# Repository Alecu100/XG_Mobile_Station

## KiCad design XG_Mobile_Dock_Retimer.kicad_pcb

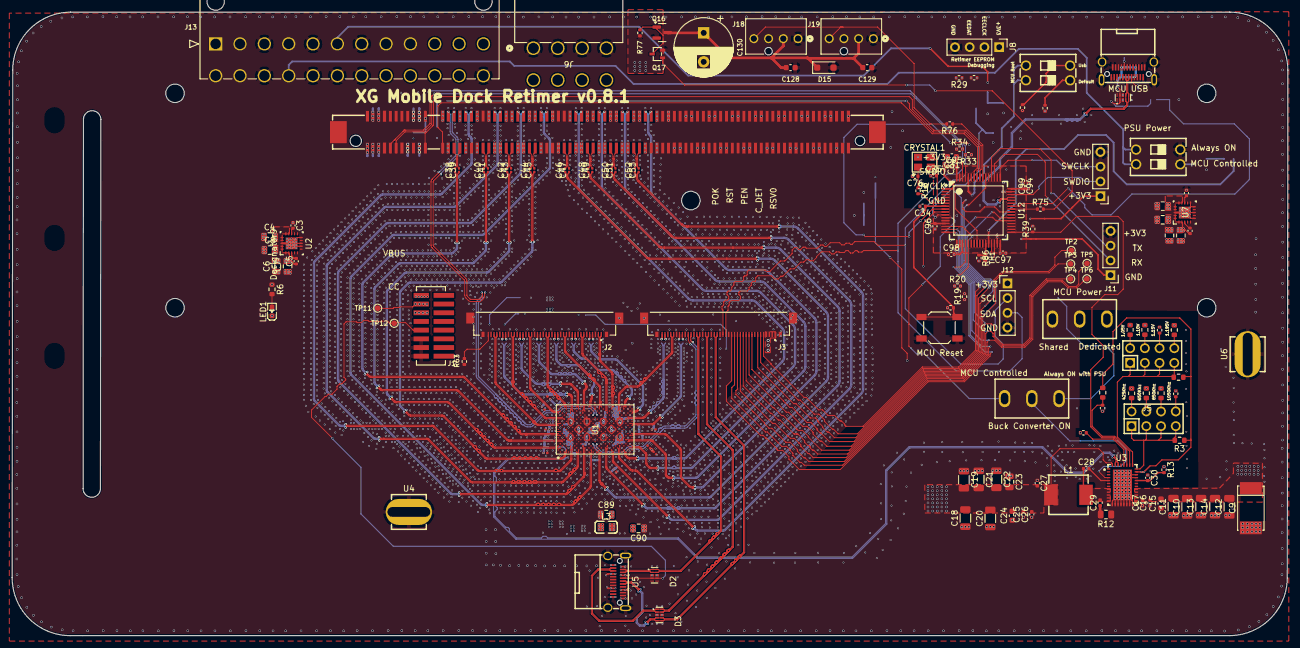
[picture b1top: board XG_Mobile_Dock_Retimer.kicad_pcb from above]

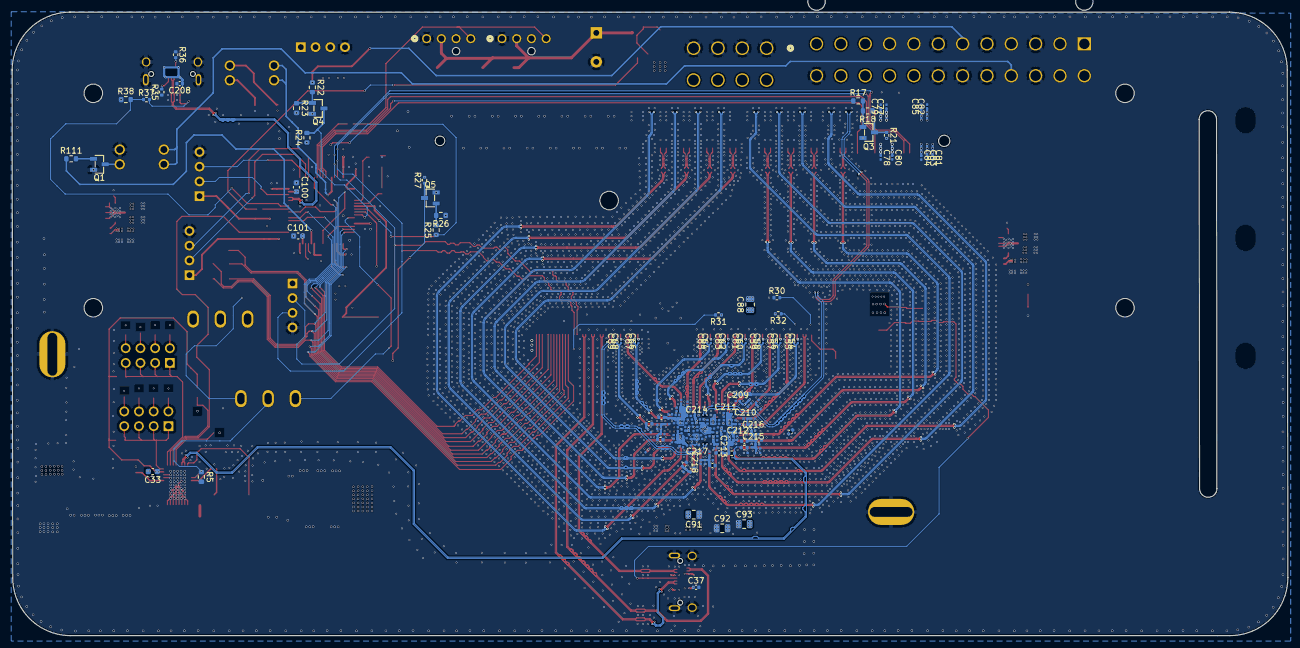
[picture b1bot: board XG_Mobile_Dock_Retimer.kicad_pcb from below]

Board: 8 copper layers, 220.1 x 107.6 mm, 324 parts (170 on the bottom side), 208 nets.

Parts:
C1, C3, C5, C70: 10nF; C_0402_1005Metric
C2, C4, C6, C71: 47uF; C_0805_2012Metric
C7, C8, C23, C72, C73, C88, C89, C90, C91, C92, C93: 10uF; C_0805_2012Metric
C9: 100uF; CAP-SMD_L7.3-W4.3
C10, C11, C12, C13, C14: 22uF; C_1206_3216Metric
C15, C33: 4.7uF; C_0603_1608Metric
C16, C25: 1uF; C_0402_1005Metric
C17, C27, C28: 0.1uF; C_0402_1005Metric
C18, C19: 220uF; C_1206_3216Metric
C20, C21: 100uF; C_1206_3216Metric
C22: 47uF; C_1206_3216Metric
C24: 3.3uF; C_0603_1608Metric
C26: 0.47uF; C_0402_1005Metric
C29: 1nFt; C_0402_1005Metric
C30: 4.7uF; C_0402_1005Metric
C31: 1µF; C_0603_1608Metric
C32, C34, C94, C95, C96, C97, C98: 0.1µF; C_0402_1005Metric
C35, C36, C74, C86, C87, C102, C103, C104, C105, C111, C112, C113, C114, C115, C116, C117, C118, C162, C163, C164, C187, C188, C201, C204, C205, C206, C209, C210, C211, C212, C213, C214, C215, C216, C217: 100nF; C_0201_0603Metric
C37, C208: 0.1μF; C_0402_1005Metric
C38, C39, C40, C41, C42, C43, C44, C45, C46, C47, C48, C49, C50, C51, C52, C53, C54, C55, C56, C57, C58, C59, C60, C61, C62, C63, C64, C65, C66, C67, C68, C69, C77, C78, C79, C80, C81, C82, C83, C84, C85: 220nF; C_0201_0603Metric
C75, C76: 15pF; C_0402_1005Metric
C99: 4.7µF; C_0402_1005Metric
C100, C101: 2.2µF; C_0603_1608Metric
C106, C107, C108, C109, C110, C192, C193, C218: 1uF; C_0201_0603Metric
C119, C120, C121, C122, C123, C124, C125, C126, C203, C207: 10uF; C_0402_1005Metric
C127, C131, C132, C133, C134, C135, C136, C137, C138, C139, C140, C141, C142, C143, C144, C145, C146, C147, C148, C149, C150, C151, C179, C180, C186: 100nF; C_0201_0603Metric_Tight
C128, C129: 0.1µF; C_0603_1608Metric
C130: 470µF; CP_Radial_D10.0mm_P5.00mm
C152, C153, C154, C155, C157, C160, C161: 100nF; C_0201_0603Metric_Tight23
C156, C158, C159, C165, C166, C167, C168, C169, C170, C171, C172, C173, C174, C175, C176, C177, C178, C181, C182, C183, C184, C185: 10nF; C_0201_0603Metric_Tight
C189, C190, C194, C195, C196, C197, C198, C199, C200: 1uF; C_0201_0603Metric_Tight
C191, C202: 1uF; C_0201_0603Metric_Tight23
CRYSTAL1: 8MHz; CRYSTAL-SMD_4P-L3.2-W2.5-BL_SIT8008BI
D1, D2, D3: H5VU25U; AZ1045-04F
D15: 1N4007; D_SOD-123F
H1, H2: HDR-TH_8P-P2.54-V-M-R2-C4-S2.54
J1: 5-1775443-8
J2, J3: 20455-040E-76
J4, J5: FL_001
J6: 353180820; CONN_SD-35318-xxxx_08_MOL
J7: CEE016400140111; CONN-SMD_164P-P1.00-CEE016400140111
J8: Retimer EEPROM; PinHeader_1x04_P2.54mm_Vertical
J10: SWD; PinHeader_1x04_P2.54mm_Vertical
J11: UART; PinHeader_1x04_P2.54mm_Vertical
J12: I2C1; PinHeader_1x04_P2.54mm_Vertical
J13: 39301240; CON_39300240
J18, J19: CONN_SD-47053-001_H10p00_MOL
L1: 1uH; IND-SMD_L7.7-W6.6_APS0630
L3: FBMJ2125HS420-T; L0805
LED1: LED0603-RD
Q1, Q3, Q4, Q5: SOT-23-3_L2.9-W1.3-P1.90-LS2.4-BR
Q16: AO3401A; SOT-23
Q17: 2N7002W; SOT-323-3_L2.0-W1.3-P1.30-LS2.1-BR
R1, R3, R9, R18, R22, R26, R38: 100k; R_0603_1608Metric
R2, R41: 133k; R_0402_1005Metric
R4, R5: 22.1k; R_0603_1608Metric
R6: 200; R_0603_1608Metric
R7: 174; R_0402_1005Metric
R8, R33, R34, R63, R77, R85: 10k; R_0402_1005Metric
R10, R37, R39: 42.2k; R_0402_1005Metric
R11: 30.1k; R_0402_1005Metric
R12: 1; R_0805_2012Metric
R13: 1; R_0402_1005Metric
R14, R15: 33; R_0201_0603Metric
R16: 150; R_0402_1005Metric
R17, R25, R111: 4k; R_0603_1608Metric
R19, R20, R21, R27, R28, R29: 4.7k; R_0402_1005Metric
R23: 470k; R_0603_1608Metric
R24: 10k; R_0603_1608Metric
R30, R31, R32, R46, R84: 1k; R_0402_1005Metric
R35, R36: 5.1k; R_0402_1005Metric
R40: 60.4k; R_0603_1608Metric
R42: 4.64k; R_0603_1608Metric
R43: 110k; R_0603_1608Metric
R44: 90.9k; R_0603_1608Metric
R45: 165k; R_0603_1608Metric
R75: 100; R_0402_1005Metric
R76: 330; R_0402_1005Metric
R86: 100k; R_0402_1005Metric
SW1: SW_Push; SW_SPST_SKQG_WithStem
SW2, SW4: SW-TH_SS-12D10L5
SW3, SW30: SW-TH_DSWB02LHGET
TH1: NCP15WF104F03RC; R_0402_1005Metric
TP2, TP3, TP4, TP5, TP6, TP11, TP12: TestPoint_Small; TestPoint_Pad_D1.0mm
U1: DS160PT801ACBR; ACB0332A-IPC_A
U2, U7: TPS7A8400ARGRR; RGR0020A
U3: LQFN-CLIP-40_L7.0-W5.0-P0.50-TL-EP
U4, U6: CONN-SMD_T31000
U5, U8: USB-C-SMD_GT-USB-7091A
U12: LQFP-64_L10.0-W10.0-P0.50-LS12.0-BL

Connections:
+1V8: C5.1, C6.2, C7.2, C8.2, C87.2, C88.1, C157.2, C160.1, C161.1, C192.1, C193.1, R6.1, R31.1, R32.2, U1.AE12 (PWR_1), U1.AF11 (PWR_1), U1.AF13 (PWR_1), U1.AG10 (PWR_1), U1.AG14 (PWR_1), U1.AH11 (PWR_1), U1.AH13 (PWR_1), U1.AJ12 (PWR_1), U1.J12 (PWR_1), U1.K11 (PWR_1), U1.K13 (PWR_1), U1.L10 (PWR_1), U1.L14 (PWR_1), U1.M11 (PWR_1), U1.M13 (PWR_1), U1.N12 (PWR_1), U2.1 (OUT), U2.2 (SNS), U2.19 (OUT), U2.20 (OUT)
+1V17_1: C93.2, C152.1, C153.1, C154.1, C155.1, C191.1, C202.1, C213.1, C214.1, L3.1, U1.AB15 (PWR_2_A), U1.AB17 (PWR_2_A), U1.AC14 (PWR_2_A), U1.AD15 (PWR_2_A), U1.AD17 (PWR_2_A), U1.P7 (PWR_2_A), U1.P9 (PWR_2_A), U1.R10 (PWR_2_A), U1.T7 (PWR_2_A), U1.T9 (PWR_2_A)
+1V17_2: C18.2, C19.2, C20.2, C21.2, C22.2, C23.2, C24.2, C25.2, C26.2, C27.2, C35.1, C36.1, C74.1, C86.1, C89.2, C90.2, C91.2, C92.2, C102.1, C103.1, C104.1, C105.1, C106.1, C107.1, C108.1, C109.1, C110.1, C111.1, C112.1, C113.1, C114.1, C115.1, C116.2, C117.2, C118.2, C119.2, C120.2, C121.2, C122.2, C123.2, C124.2, C125.2, C126.2, C127.1, C131.1, C132.1, C133.1, C134.1, C135.1, C136.1, C137.1, C138.1, C139.1, C140.1, C141.1, C142.1, C143.1, C144.1, C145.1, C146.1, C147.1, C148.1, C149.1, C150.1, C151.1, C156.2, C158.2, C159.2, C162.2, C163.2, C164.2, C165.2, C166.2, C167.2, C168.2, C169.2, C170.2, C171.2, C172.2, C173.2, C174.2, C175.2, C176.2, C177.2, C178.2, C179.1, C180.1, C181.2, C182.2, C183.2, C184.2, C185.2, C186.1, C187.2, C188.2, C189.2, C190.2, C194.2, C195.1, C196.1, C197.1, C198.1, C199.2, C200.1, C201.2, C203.2, C204.2, C205.2, C206.2, C207.2, C209.2, C210.2, C211.2, C212.2, C215.2, C216.2, C217.2, C218.2, L1.1, L3.2, R7.1, U1.AA12 (PWR2_HS_D), U1.AB7 (PWR2_HS_A), U1.AB9 (PWR2_HS_A), U1.AC10 (PWR2_HS_D), U1.AD7 (PWR2_HS_A), U1.AD9 (PWR2_HS_A), U1.AK7 (PWR2_HS_A), U1.AK9 (PWR2_HS_D), U1.AK15 (PWR2_HS_D), U1.AK17 (PWR2_HS_A), U1.AL10 (PWR2_HS_D), U1.AL14 (PWR2_HS_D), U1.AM7 (PWR2_HS_A), U1.AM9 (PWR2_HS_D), U1.AM15 (PWR2_HS_D), U1.AM17 (PWR2_HS_A), U1.F7 (PWR2_HS_A), U1.F9 (PWR2_HS_D), U1.F15 (PWR2_HS_D), U1.F17 (PWR2_HS_A), U1.G10 (PWR2_HS_D), U1.G14 (PWR2_HS_D), U1.H7 (PWR2_HS_A), U1.H9 (PWR2_HS_D), U1.H15 (PWR2_HS_D), U1.H17 (PWR2_HS_A), U1.P15 (PWR2_HS_A), U1.P17 (PWR2_HS_A), U1.R14 (PWR2_HS_D), U1.T15 (PWR2_HS_A), U1.T17 (PWR2_HS_A), U1.U12 (PWR2_HS_D), U1.V11 (PWR2_HS_D), U1.V13 (PWR2_HS_A), U1.W10 (PWR2_HS_A), U1.W14 (PWR2_HS_A), U1.Y11 (PWR2_HS_A), U1.Y13 (PWR2_HS_D), U3.40 (VOSNS)
+3V3: C4.2, C77.1, C78.1, C79.1, C80.1, J7.A9, J7.A10, J7.B8, J7.B10, J8.1, J13.1, J13.2, J13.12, J13.13, R21.2, R27.2, R28.2, R29.2, SW2.3, SW4.3, U2.14 (EN), U2.15 (IN), U2.16 (IN), U2.17 (IN)
+3V3MCU: C31.1, C32.2, C94.2, C95.2, C96.2, C97.2, C98.2, C99.1, J3.1 (+3.3V), J3.2 (+3.3V), J3.3 (+3.3V), J3.4 (+3.3V), J10.1, J11.1, J12.1, R19.1, R20.1, R24.1, R33.1, R34.1, R39.2, R46.1, R85.2, R86.2, SW4.2, U12.1 (VBAT), U12.13 (VDDA), U12.19 (VDD), U12.32 (VDD), U12.48 (VDD), U12.64 (VDD)
+3V3SB: C70.1, C71.2, C72.2, C73.2, SW4.1, U7.1 (OUT), U7.2 (SNS), U7.19 (OUT), U7.20 (OUT)
+5VSB: C2.2, J13.9, U7.14 (EN), U7.15 (IN), U7.16 (IN), U7.17 (IN)
+12V: C9.1, C10.2, C11.2, C12.2, C13.2, C14.2, C15.2, C16.2, C17.2, C81.1, C82.1, C83.1, C84.1, C85.1, J6.5, J6.6, J6.7, J6.8, J7.A2, J7.A3, J7.B1, J7.B2, J7.B3, J13.10, J13.11, Q16.2 (S), R13.1, R77.1, U3.21 (PVIN), U3.22 (PVIN), U3.23 (PVIN), U3.24 (PVIN), U3.25 (PVIN)
/AC_LOSS: J3.15 (P_AC_LOSS), U12.20 (PA4)
/BP: C33.1, R1.1, R3.1, R9.1, U3.31 (BP)
/BUCK_ON: R5.1, SW2.2, U3.4 (EN_UVLO)
/BUCK_ON_MCU: SW2.1, U12.11 (PC3)
/CC: D2.4 (I/O_3), D2.7 (NC), J1.13 (CC), TP12.1 (1_1), U5.A5 (CC1)
/CLKN: J3.30 (PCIE_CLKN), U1.V5 (REFCLK-)
/CLKOUTN: J7.A14, R15.2
/CLKOUTP: J7.A13, R14.2
/CLKOUT_T_N: R15.1, U1.V19 (REFCLKOUT-)
/CLKOUT_T_P: R14.1, U1.Y19 (REFCLKOUT+)
/CLKP: J3.31 (PCIE_CLKP), U1.Y5 (REFCLK+)
/CLKREQ#: J7.B12, U12.58 (PB6)
/CLKREQ_RETIMER#: U1.B11 (CLKREQ_N), U12.9 (PC1)
/CON_DET: J3.11 (CON_DET), TP3.1 (1_1), U12.14 (PA0-WKUP(PA0))
/C_DN: D3.5 (I/O_4), D3.6 (NC), J3.21 (USB_DM), U5.A7 (D-)
/C_DP: D3.4 (I/O_3), D3.7 (NC), J3.22 (USB_DP), U5.A6 (D+)
/C_RXN: D3.2 (I/O_2), D3.9 (NC), J3.24 (USB_RXN), U5.B11 (Rx1+)
/C_RXP: D3.1 (I/O_1), D3.10 (NC), J3.25 (USB_RXP), U5.B10 (RX1-)
/C_TXN: D2.1 (I/O_1), D2.10 (NC), J3.28 (USB_TXP), U5.A2 (TX1+)
/C_TXP: D2.2 (I/O_2), D2.9 (NC), J3.27 (USB_TXN), U5.A3 (TX1-)
/DET: J2.40 (CON_DET_TOWER#), R63.1
/EE_CLCK: J8.2, R28.1, U1.AP11 (EE_CLK)
/EE_DAT: J8.3, R29.1, U1.AP13 (EE_DAT)
/FSEL: H2.1, H2.3, H2.5, H2.7, R3.2, U3.32 (FSEL)
/HSI0N: C55.2, J2.34 (PCIE_RXN0)
/HSI0P: C54.2, J2.35 (PCIE_RXP0)
/HSI1N: C57.2, J2.28 (PCIE_RXN1)
/HSI1P: C56.2, J2.29 (PCIE_RXP1)
/HSI2N: C59.2, J2.22 (PCIE_RXN2)
/HSI2P: C58.2, J2.23 (PCIE_RXP2)
/HSI3N: C61.2, J2.16 (PCIE_RXN3)
/HSI3P: C60.2, J2.17 (PCIE_RXP3)
/HSI4N: C63.2, J2.10 (PCIE_RXN4)
/HSI4P: C62.2, J2.11 (PCIE_RXP4)
/HSI5N: C65.2, J2.4 (PCIE_RXN5)
/HSI5P: C64.2, J2.5 (PCIE_RXP5)
/HSI6N: C67.2, J3.39 (PCIE_RXN6)
/HSI6P: C66.2, J3.40 (PCIE_RXP6)
/HSI7N: C69.2, J3.33 (PCIE_RXN7)
/HSI7P: C68.2, J3.34 (PCIE_RXP7)
/HSIL0N: J7.A17, U1.G4 (B_PERn0)
/HSIL0P: J7.A16, U1.H3 (B_PERp0)
/HSIL1N: J7.A22, U1.K1 (B_PERn1)
/HSIL1P: J7.A21, U1.L2 (B_PERp1)
/HSIL2N: J7.A26, U1.N4 (B_PERn2)
/HSIL2P: J7.A25, U1.P3 (B_PERp2)
/HSIL3N: J7.A30, U1.T1 (B_PERn3)
/HSIL3P: J7.A29, U1.U2 (B_PERp3)
/HSIL4N: J7.A36, U1.AN2 (B_PERn4)
/HSIL4P: J7.A35, U1.AP1 (B_PERp4)
/HSIL5N: J7.A40, U1.AT3 (B_PERn5)
/HSIL5P: J7.A39, U1.AU4 (B_PERp5)
/HSIL6N: J7.A44, U1.AR6 (B_PERn6)
/HSIL6P: J7.A43, U1.AP7 (B_PERp6)
/HSIL7N: J7.A48, U1.AT9 (B_PERn7)
/HSIL7P: J7.A47, U1.AU10 (B_PERp7)
/HSIT0N: C55.1, U1.H21 (B_PETp0)
/HSIT0P: C54.1, U1.G20 (B_PETn0)
/HSIT1N: C57.1, U1.L22 (B_PETp1)
/HSIT1P: C56.1, U1.K23 (B_PETn1)
/HSIT2N: C59.1, U1.P21 (B_PETp2)
/HSIT2P: C58.1, U1.N20 (B_PETn2)
/HSIT3N: C61.1, U1.U22 (B_PETp3)
/HSIT3P: C60.1, U1.T23 (B_PETn3)
/HSIT4N: C63.1, U1.AP23 (B_PETp4)
/HSIT4P: C62.1, U1.AN22 (B_PETn4)
/HSIT5N: C65.1, U1.AU20 (B_PETp5)
/HSIT5P: C64.1, U1.AT21 (B_PETn5)
/HSIT6N: C67.1, U1.AP17 (B_PETp6)
/HSIT6P: C66.1, U1.AR18 (B_PETn6)
/HSIT7N: C69.1, U1.AU14 (B_PETp7)
/HSIT7P: C68.1, U1.AT15 (B_PETn7)
/HSO0N: C39.2, J7.B15
/HSO0P: C38.2, J7.B14
/HSO1N: C41.2, J7.B20
/HSO1P: C40.2, J7.B19
/HSO2N: C43.2, J7.B24
/HSO2P: C42.2, J7.B23
/HSO3N: C45.2, J7.B28
/HSO3P: C44.2, J7.B27
/HSO4N: C47.2, J7.B34
/HSO4P: C46.2, J7.B33
/HSO5N: C49.2, J7.B38
/HSO5P: C48.2, J7.B37
/HSO6N: C51.2, J7.B42
/HSO6P: C50.2, J7.B41
/HSO7N: C53.2, J7.B46
/HSO7P: C52.2, J7.B45
/HSOL0N: J2.37 (PCIE_TXN0), U1.B15 (A_PERp0)
/HSOL0P: J2.38 (PCIE_TXP0), U1.A14 (A_PERn0)
/HSOL1N: J2.31 (PCIE_TXN1), U1.C18 (A_PERp1)
/HSOL1P: J2.32 (PCIE_TXP1), U1.D17 (A_PERn1)
/HSOL2N: J2.25 (PCIE_TXN2), U1.B21 (A_PERp2)
/HSOL2P: J2.26 (PCIE_TXP2), U1.A20 (A_PERn2)
/HSOL3N: J2.19 (PCIE_TXN3), U1.E22 (A_PERp3)
/HSOL3P: J2.20 (PCIE_TXP3), U1.D23 (A_PERn3)
/HSOL4N: J2.13 (PCIE_TXN4), U1.AB23 (A_PERp4)
/HSOL4P: J2.14 (PCIE_TXP4), U1.AA22 (A_PERn4)
/HSOL5N: J2.7 (PCIE_TXN5), U1.AE20 (A_PERp5)
/HSOL5P: J2.8 (PCIE_TXP5), U1.AD21 (A_PERn5)
/HSOL6N: J2.1 (PCIE_TXN6), U1.AH23 (A_PERp6)
/HSOL6P: J2.2 (PCIE_TXP6), U1.AG22 (A_PERn6)
/HSOL7N: J3.36 (PCIE_TXN7), U1.AL20 (A_PERp7)
/HSOL7P: J3.37 (PCIE_TXP7), U1.AK21 (A_PERn7)
/HSOT0N: C39.1, U1.A10 (A_PETn0)
/HSOT0P: C38.1, U1.B9 (A_PETp0)
/HSOT1N: C41.1, U1.D7 (A_PETn1)
/HSOT1P: C40.1, U1.C6 (A_PETp1)
/HSOT2N: C43.1, U1.A4 (A_PETn2)
/HSOT2P: C42.1, U1.B3 (A_PETp2)
/HSOT3N: C45.1, U1.D1 (A_PETn3)
/HSOT3P: C44.1, U1.E2 (A_PETp3)
/HSOT4N: C47.1, U1.AA2 (A_PETn4)
/HSOT4P: C46.1, U1.AB1 (A_PETp4)
/HSOT5N: C49.1, U1.AD3 (A_PETn5)
/HSOT5P: C48.1, U1.AE4 (A_PETp5)
/HSOT6N: C51.1, U1.AG2 (A_PETn6)
/HSOT6P: C50.1, U1.AH1 (A_PETp6)
/HSOT7N: C53.1, U1.AK3 (A_PETn7)
/HSOT7P: C52.1, U1.AL4 (A_PETp7)
/LED_RED#: J3.7 (LED_R), U12.54 (PD2)
/LED_WHITE#: J3.6 (LED_W), U12.40 (PC9)
/LOCK_DET: J3.9 (CON_SW1_DET), U12.37 (PC6)
/LOCK_SW: J3.5 (LOCK_SW), U12.24 (PC4)
/MCU_IRQ#: J3.16 (MCU_IRQ#), U12.21 (PA5)
/MCU_Retimer/BOOT0: SW3.1, SW3.2, U12.60 (BOOT0)
/MCU_Retimer/FAN_ON: R75.1, U12.41 (PA8)
/MCU_Retimer/FAN_PWM: R76.1, U12.55 (PB3(JTDOTRACESWO))
/MCU_Retimer/RX: J11.3, U12.52 (PC11)
/MCU_Retimer/SWCLK: J10.3, U12.49 (PA14(JTCK-SWCLK))
/MCU_Retimer/SWDIO: J10.2, U12.46 (PA13(JTMS-SWDIO))
/MCU_Retimer/TX: J11.2, U12.51 (PC10)
/MODE: R9.2, R10.1, U3.34 (MODE)
/PERST#: J7.A11, Q3.3 (C), R21.1
/PERST_MCU#: R17.1, U12.57 (PB5)
/PERST_RETIMER#: Q5.3 (C), R27.1, U1.Y1 (PERST_N)
/PERST_RETIMER_MCU#: R25.1, U12.8 (PC0)
/PGOOD_BUCK: R39.1, U3.35 (PGOOD), U12.33 (PB12)
/PRE_IN: C28.1, C29.2, L1.2, U3.8 (SW), U3.9 (SW), U3.10 (SW), U3.11 (SW), U3.12 (SW)
/PSON: R111.1, U12.28 (PB2-BOOT1(PB2))
/PSPWROK: J13.6, R22.1
/PSPWROK3V3: Q4.3 (C), R24.2, U12.10 (PC2)
/PWREN#: J3.12 (PWR_EN#), TP4.1 (1_1), U12.15 (PA1)
/PWROK: J3.14 (PWROK), TP6.1 (1_1), U12.17 (PA3)
/RSP: R7.2, R8.1, U3.39 (RSP)
/RST#: J3.13 (RST#), TP5.1 (1_1), U12.16 (PA2)
/RST_SW: C34.1, R85.1, SW1.1, U12.7 (NRST)
/RSV0: J3.10, TP2.1 (1_1), U12.38 (PC7)
/SCL: J3.19 (SMB1_CLK), J7.B5, J12.2, R33.2, U12.61 (PB8)
/SCL2: R19.2, U1.AC6 (SMBCLK), U12.29 (PB10)
/SDA: J3.18 (SMB1_DAT), J7.B6, J12.3, R34.2, U12.62 (PB9)
/SDA2: R20.2, U1.AG6 (SMBDAT), U12.30 (PB11)
/USBDN: D1.4 (I/O_3), D1.7 (NC), U8.A7 (D-), U12.44 (PA11)
/USBDP: D1.5 (I/O_4), D1.6 (NC), U8.A6 (D+), U12.45 (PA12)
/USBVBUS: R37.1, R38.2, U12.42 (PA9)
/VBUS: C37.1, J1.9 (VBUS), J1.10 (VBUS), J1.11 (VBUS), TP11.1 (1_1), U5.A4 (VBUS), U5.A9 (VBUS), U5.B4 (VBUS), U5.B9 (VBUS)
/VBUS_USB2: C208.1, D1.2 (I/O_2), D1.9 (NC), R37.2, U8.A4 (VBUS), U8.A9 (VBUS), U8.B4 (VBUS), U8.B9 (VBUS)
/VSEL: H1.1, H1.3, H1.5, H1.7, R1.2, U3.33 (VSEL)
/WAKE#: J7.B11, U12.56 (PB4(NJTRST))
GND: C1.1, C2.1, C3.1, C4.1, C6.1, C7.1, C8.1, C9.2, C10.1, C11.1, C12.1, C13.1, C14.1, C15.1, C16.1, C17.1, C18.1, C19.1, C20.1, C21.1, C22.1, C23.1, C24.1, C25.1, C26.1, C27.1, C30.1, C31.2, C32.1, C33.2, C34.2, C35.2, C36.2, C37.2, C71.1, C72.1, C73.1, C74.2, C75.1, C76.2, C77.2, C78.2, C79.2, C80.2, C81.2, C82.2, C83.2, C84.2, C85.2, C86.2, C87.1, C88.2, C89.1, C90.1, C91.1, C92.1, C93.1, C94.1, C95.1, C96.1, C97.1, C98.1, C99.2, C100.1, C101.1, C102.2, C103.2, C104.2, C105.2, C106.2, C107.2, C108.2, C109.2, C110.2, C111.2, C112.2, C113.2, C114.2, C115.2, C116.1, C117.1, C118.1, C119.1, C120.1, C121.1, C122.1, C123.1, C124.1, C125.1, C126.1, C127.2, C128.2, C129.2, C130.2, C131.2, C132.2, C133.2, C134.2, C135.2, C136.2, C137.2, C138.2, C139.2, C140.2, C141.2, C142.2, C143.2, C144.2, C145.2, C146.2, C147.2, C148.2, C149.2, C150.2, C151.2, C152.2, C153.2, C154.2, C155.2, C156.1, C157.1, C158.1, C159.1, C160.2, C161.2, C162.1, C163.1, C164.1, C165.1, C166.1, C167.1, C168.1, C169.1, C170.1, C171.1, C172.1, C173.1, C174.1, C175.1, C176.1, C177.1, C178.1, C179.2, C180.2, C181.1, C182.1, C183.1, C184.1, C185.1, C186.2, C187.1, C188.1, C189.1, C190.1, C191.2, C192.2, C193.2, C194.1, C195.2, C196.2, C197.2, C198.2, C199.1, C200.2, C201.1, C202.2, C203.1, C204.1, C205.1, C206.1, C207.1, C208.2, C209.1, C210.1, C211.1, C212.1, C213.2, C214.2, C215.1, C216.1, C217.1, C218.1, CRYSTAL1.2 (GND), CRYSTAL1.4 (GND), D1.3 (GND), D1.8 (GND), D2.3 (GND), D2.8 (GND), D3.3 (GND), D3.8 (GND), D15.2 (A), J1.14 (GND), J1.15 (GND), J1.16 (GND), J2.3 (GND), J2.6 (GND), J2.9 (GND), J2.12 (GND), J2.15 (GND), J2.18 (GND), J2.21 (GND), J2.24 (GND), J2.27 (GND), J2.30 (GND), J2.33 (GND), J2.36 (GND), J2.39 (GND), J2.S1 (SHIELD), J2.S2 (SHIELD), J2.S3 (SHIELD), J2.S4 (SHIELD), J3.17 (GND), J3.20 (GND), J3.23 (GND), J3.26 (GND), J3.29 (GND), J3.32 (GND), J3.35 (GND), J3.38 (GND), J3.S1 (SHIELD), J3.S2 (SHIELD), J3.S3 (SHIELD), J3.S4 (SHIELD), J6.1, J6.2, J6.3, J6.4, J7.2, J7.A4, J7.A12, J7.A15, J7.A18, J7.A20, J7.A23, J7.A24, J7.A27, J7.A28, J7.A31, J7.A34, J7.A37, J7.A38, J7.A41, J7.A42, J7.A45, J7.A46, J7.A49, J7.A51, J7.A54, J7.A55, J7.A58, J7.A59, J7.A62, J7.A63, J7.A66, J7.A67, J7.A70, J7.A71, J7.A74, J7.A75, J7.A78, J7.A79, J7.A82, J7.B4, J7.B7, J7.B13, J7.B16, J7.B18, J7.B21, J7.B22, J7.B25, J7.B26, J7.B29, J7.B32, J7.B35, J7.B36, J7.B39, J7.B40, J7.B43, J7.B44, J7.B47, J7.B49, J7.B52, J7.B53, J7.B56, J7.B57, J7.B60, J7.B61, J7.B64, J7.B65, J7.B68, J7.B69, J7.B72, J7.B73, J7.B76, J7.B77, J7.B80, J8.4, J10.4, J11.4, J12.4, J13.3, J13.5, J13.7, J13.15, J13.17, J13.18, J13.19, J13.24, J18.1, J19.1, LED1.1 (K), Q1.2 (E), Q3.2 (E), Q4.2 (E), Q5.2 (E), Q17.2 (S), R2.2, R4.2, R5.2, R8.2, R10.2, R11.1, R12.1, R18.1, R23.2, R26.1, R30.1, R35.1, R36.1, R38.1, R40.2, R41.2, R42.2, R43.2, R44.2, R45.2, R63.2, R84.1, SW1.2, SW30.4, TH1.2, U1.A2 (GND), U1.A8 (GND), U1.A16 (GND), U1.A22 (GND), U1.AA4 (GND), U1.AA8 (GND), U1.AA16 (GND), U1.AA20 (GND), U1.AB3 (GND), U1.AB5 (GND), U1.AB11 (GND), U1.AB13 (GND), U1.AB19 (GND), U1.AB21 (GND), U1.AC2 (GND), U1.AC22 (GND), U1.AD5 (GND), U1.AD11 (GND), U1.AD13 (GND), U1.AD19 (GND), U1.AE8 (GND), U1.AE16 (GND), U1.AF1 (GND), U1.AF3 (GND), U1.AF5 (GND), U1.AF7 (GND), U1.AF9 (GND), U1.AF15 (GND), U1.AF17 (GND), U1.AF19 (GND), U1.AF21 (GND), U1.AF23 (GND), U1.AH3 (GND), U1.AH5 (GND), U1.AH7 (GND), U1.AH9 (GND), U1.AH15 (GND), U1.AH17 (GND), U1.AH19 (GND), U1.AH21 (GND), U1.AJ2 (GND), U1.AJ4 (GND), U1.AJ8 (GND), U1.AJ16 (GND), U1.AJ20 (GND), U1.AJ22 (GND), U1.AK5 (GND), U1.AK11 (GND), U1.AK13 (GND), U1.AK19 (GND), U1.AL6 (GND), U1.AL18 (GND), U1.AM1 (GND), U1.AM3 (GND), U1.AM5 (GND), U1.AM11 (GND), U1.AM13 (GND), U1.AM19 (GND), U1.AM21 (GND), U1.AM23 (GND), U1.AN4 (GND), U1.AN8 (GND), U1.AN12 (GND), U1.AN16 (GND), U1.AN20 (GND), U1.AP5 (GND), U1.AP9 (GND), U1.AP15 (GND), U1.AP19 (GND), U1.AR2 (GND), U1.AR4 (GND), U1.AR8 (GND), U1.AR10 (GND), U1.AR14 (GND), U1.AR16 (GND), U1.AR20 (GND), U1.AR22 (GND), U1.AT1 (GND_NC), U1.AT5 (GND), U1.AT11 (GND), U1.AT19 (GND), U1.AT23 (GND_NC), U1.AU2 (GND), U1.AU8 (GND), U1.AU16 (GND), U1.AU22 (GND), U1.B1 (GND_NC), U1.B5 (GND), U1.B13 (GND), U1.B19 (GND), U1.B23 (GND_NC), U1.C2 (GND), U1.C4 (GND), U1.C8 (GND), U1.C10 (GND), U1.C14 (GND), U1.C16 (GND), U1.C20 (GND), U1.C22 (GND), U1.D5 (GND), U1.D9 (GND), U1.D15 (GND), U1.D19 (GND), U1.E4 (GND), U1.E8 (GND), U1.E12 (GND), U1.E20 (GND), U1.F1 (GND), U1.F3 (GND), U1.F5 (GND), U1.F11 (GND), U1.F13 (GND), U1.F19 (GND), U1.F21 (GND), U1.F23 (GND), U1.G6 (GND), U1.G18 (GND), U1.H5 (GND), U1.H11 (GND), U1.H13 (GND), U1.H19 (GND), U1.J2 (GND), U1.J4 (GND), U1.J8 (GND), U1.J16 (GND), U1.J20 (GND), U1.J22 (GND), U1.K3 (GND), U1.K5 (GND), U1.K7 (GND), U1.K9 (GND), U1.K15 (GND), U1.K17 (GND), U1.K19 (GND), U1.K21 (GND), U1.M1 (GND), U1.M3 (GND), U1.M5 (GND), U1.M7 (GND), U1.M9 (GND), U1.M15 (GND), U1.M17 (GND), U1.M19 (GND), U1.M21 (GND), U1.M23 (GND), U1.N8 (GND), U1.N16 (GND), U1.P5 (GND), U1.P11 (GND), U1.P13 (GND), U1.P19 (GND), U1.R2 (GND), U1.R22 (GND), U1.T3 (GND), U1.T5 (GND), U1.T11 (GND), U1.T13 (GND), U1.T19 (GND), U1.T21 (GND), U1.U4 (GND), U1.U8 (GND), U1.U16 (GND), U1.U20 (GND), U1.V1 (GND), U1.V3 (GND), U1.V7 (GND), U1.V9 (GND), U1.V15 (GND), U1.V17 (GND), U1.V21 (GND), U1.W6 (GND), U1.W18 (GND), U1.Y3 (GND), U1.Y7 (GND), U1.Y9 (GND), U1.Y15 (GND), U1.Y17 (GND), U1.Y21 (GND), U1.Y23 (GND), U2.7 (200_mV), U2.8 (GND), U2.10 (800_mV), U2.18 (GND), U2.21 (PAD), U3.13 (PGND), U3.14 (PGND), U3.15 (PGND), U3.16 (PGND), U3.17 (PGND), U3.18 (PGND), U3.19 (PGND), U3.20 (PGND), U3.29 (DRGND), U3.30 (AGND), U3.38 (RSN), U3.41 (EP), U4.1 (1_1), U5.1 (EH), U5.2 (EH), U5.3 (EH), U5.4 (EH), U5.A1 (GND), U5.A12 (GND), U5.B1 (GND), U5.B12 (GND), U6.1 (1_1), U7.6 (100_mV), U7.8 (GND), U7.10 (800_mV), U7.11 (1.6_V), U7.18 (GND), U7.21 (PAD), U8.1 (EH), U8.2 (EH), U8.3 (EH), U8.4 (EH), U8.A1 (GND), U8.A12 (GND), U8.B1 (GND), U8.B12 (GND), U12.12 (VSSA), U12.18 (VSS), U12.63 (VSS)
unnamed: C29.1, R12.2
unnamed: C76.1, CRYSTAL1.1, R16.1
unnamed: C128.1, C129.1, C130.1, D15.1 (K), J18.2, J19.2, Q16.3 (D)
unnamed: H1.2, R44.1
unnamed: H1.4, R43.1
unnamed: H1.6, R2.1
unnamed: H1.8, R45.1
unnamed: H2.2, R42.1
unnamed: H2.4, R4.1
unnamed: H2.6, R40.1
unnamed: H2.8, R41.1
unnamed: J13.16, SW30.1, SW30.2
unnamed: J18.4, J19.4, R76.2
unnamed: LED1.2 (A), R6.2
unnamed: Q1.1 (B), R111.2
unnamed: Q1.3 (C), SW30.3
unnamed: Q3.1 (B), R17.2, R18.2
unnamed: Q4.1 (B), R22.2, R23.1
unnamed: Q5.1 (B), R25.2, R26.2
unnamed: Q16.1 (G), Q17.3 (D), R77.2
unnamed: Q17.1 (G), R75.2
unnamed: R46.2, SW3.4
unnamed: R84.2, SW3.3
unnamed: R30.2, U1.R18 (JTAG_TRST_N)
unnamed: R31.2, U1.AU12 (PRT0_RST_N)
unnamed: R32.1, U1.W22 (PRT1_RST_N)
unnamed: C5.2, U2.3 (FB)
unnamed: C3.2, U2.13 (NR_SS)
unnamed: C28.2, U3.5 (BOOT)
unnamed: R11.2, U3.36 (ILIM)
unnamed: C30.2, R13.2, U3.28 (VDD)
unnamed: C70.2, U7.3 (FB)
unnamed: C1.2, U7.13 (NR_SS)
unnamed: R35.2, U8.A5 (CC1)
unnamed: R36.2, U8.B5 (CC2)
unnamed: R86.1, TH1.1, U12.27 (PB1)
unnamed: C75.2, CRYSTAL1.3, U12.5 (PH0-OSC_IN(PH0))
unnamed: R16.2, U12.6 (PH1-OSC_OUT(PH1))
unnamed: C101.2, U12.31 (VCAP_1)
unnamed: C100.2, U12.47 (VCAP_2)
